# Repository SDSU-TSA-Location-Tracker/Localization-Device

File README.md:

# Localization-Device
This pocket embedded device acts as a local node in a network of anchor nodes and a gateway node. The local device transmits data to the anchor nodes, which measure the RSSI between multiple anchor nodes and the local node to estimate the distance between anchors in the network; this estimation is done through a classification machine learning model. The transmission and receiving of data between local and anchor nodes will be performed using BLE technology. The distance estimation is done at the gateway node, where the RSSI values are sent. One layer up, a holistic system calculates the position of the local node based on the distance from each anchor node. Our design utilizes embedded design with microcontrollers, power and networking components, and networking and machine learning algorithms. 

## Project Team Members
Leonard Chatterton (CompE), Hada Marabeh (EE), Tristan Richmond (CompE), Sri Shatagopam (CompE), Zachary Rocha (EE)
 
## How to Contribute to the Repository
Here is a brief explanation on how to contribute git and github

#### Git vs. Github
Git is a repository version control that is local to your computer only. This means only the user of the local computer has access to these files. It keeps track of any changes that are commited to it so that each iteration of a repo can be accessed. Be sure to update this each time you finish your work session for the day as it will act as a backup storage. Git is important for version control but also because this is where github will be pulling the files from whenever a "push" occurs. **You will need to install git onto your computer**

https://git-scm.com/downloads

Github is a cloud based repository viewer that holds allows a repository to be accessed via webapp. Github will act as a central location for all our individual tasks and develepments to be accessed from any computer connected to the internet. Changes should be comitted to Git first and then it is pushed to Github so anybody can access the actual files. 

#### Cloning
To make the initial link of a github repository onto your git, you must clone it. Here are the steps to doing so

1. Open git bash or linux terminal in the working directory of where you wish to store the repository files on your computer. This is can be done by right-clicking inside the folder you save the files and selecting "Git Bash Here"

2. Use the clone command to clone the github repository onto your git. It will automatically create a folder with the name of the repository with all of its contents
```
git clone https://github.com/SDSU-TSA-Location-Tracker/Localization-Device.git
```

#### Branching
Every repository, in our case **Localization-Device**, has a **main** branch where the most up-to-date ready to ship version is held. This is to ensure there is always a deployable version at any point in the development and maintenance cycle. When new features or additions are being developed, typically a new branch is created with the name of that feature. This allows for a new location that new code and updates can be saved without affecting the **main** branch. In our case, there currently exists a branch for each seperate piece to the project. Once one of the features/branches has been thoroughly tested and is stable, that branch is merged into the **main** branch. What this will do is copy all files from the initial development branch and merge them into the **main** branch so it becomes the most up-to-date version with these new features.

Here is an example of how to create a new branch off of main. Please use the following naming format for the branch **[Your_Name]_[Description of Branch]**

#### Github Branch Example

Create a new branch off of **RaspberryPi** called "Tristan_RaspberryPi_PCB_Design"

```
git checkout -b Tristan_RaspberryPi_PCB_Design RaspberryPi
```

#### Git Workflow

Here is a step by step explanation of how a typical worksession goes

1. Open git bash or linux terminal in the working directory of where you store the repository files on your computer. This is can be done by right-clicking inside the folder you save the files and selecting "Git Bash Here"

2. Pull any and all changes from the github repository **main** to be saved into your local git. Note you must enter the exact branches you wish to update your local version of to the github version. See step 3 on how to change current branch. 
```
git pull origin [Name_of_Branch]
```

3. Enter the exact branch you wish to do development in. Important to do this step as failure to do so may result in conflicts
```
git checkout [Name_of_Branch]
```

4. Start developing as you normally do until you are all finished

5. Add the specific files that were worked
```
git add file.txt
```

6. Commit the changes to the added files to the local git with a message of what was changed. It is important to add a message as the commit will open up VIM expecting you to write a message in. **To avoid this issue, be sure to write the message in the initial commit command**
```
git commit -m "Programmed the Arduino to blink an LED every 5 seconds"
```

7. Push these commits in your local git to the github so everyone can pull these changes to their local computers
```
git push origin [Name_of_Branch]
```

8. A pop window will appear prompting for you github login information. Enter you username into the first window and click submit, then enter you password into the second window and click submit.

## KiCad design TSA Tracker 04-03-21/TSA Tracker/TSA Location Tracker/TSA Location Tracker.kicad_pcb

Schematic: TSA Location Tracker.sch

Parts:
Arduino1: Arduino-NANO-33; NANO_33_Socket_Castell
D1: LED; LED_D3.0mm
H1, H2, H3, H4: MountingHole_Pad; MountingHole_2.7mm_M2.5_Pad
LED_Switch1: SW_SPST; SW_PUSH_6mm
Mode_Switch1: SW_SP3T; E-Switch-EG1313-0
Power_Switch1: SW_DPDT_x2; SW_CuK_JS202011AQN_DPDT_Angled
R1, R2, R3, R5: 10k; R_0603_1608Metric_Pad1.05x0.95mm_HandSolder
R4: 330; R_0603_1608Metric_Pad1.05x0.95mm_HandSolder
U1: AdafruitCharger; AdafruitMiniLipo

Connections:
GND: Arduino1.14, H1.1, H2.1, H3.1, H4.1, R1.2, R2.2, R3.2, R5.2, U1.2, U1.3
unnamed: Arduino1.2, LED_Switch1.2, Mode_Switch1.3, Power_Switch1.3 (C)
unnamed: Arduino1.19, D1.1 (K)
unnamed: Arduino1.20, R4.2
unnamed: Arduino1.21, LED_Switch1.1, R5.1
unnamed: Arduino1.26, Mode_Switch1.4, R1.1
unnamed: Arduino1.27, Mode_Switch1.2, R2.1
unnamed: Arduino1.28, Mode_Switch1.1, R3.1
unnamed: D1.2 (A), R4.1
unnamed: Power_Switch1.2 (B), U1.4

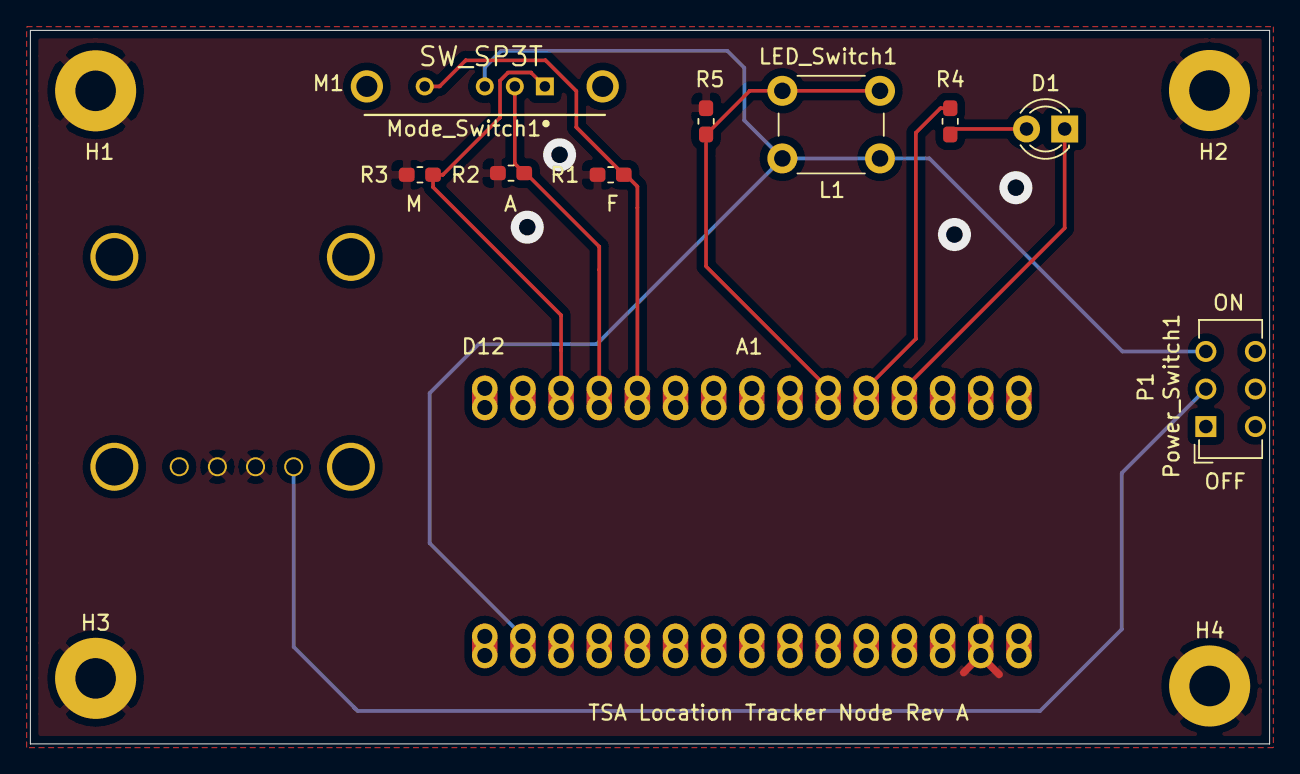
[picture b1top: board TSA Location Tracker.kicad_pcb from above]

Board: 2 copper layers, 82.5 x 47.5 mm, 15 parts (1 on the bottom side), 10 nets.

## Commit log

2021-03-17 Old version
2021-03-17 Added data routine, PCB verification, and node firmware files
2021-03-17 Added RaspberryPi scan firmware
2021-03-19 Fixed RSSI value format to '-70'
2021-03-26 working data collection update
2021-03-30 Data Routine mode switch features
2021-03-30 In progress changes to Node Firmware
2021-03-30 Scan for all BLE devices on RPi4
2021-03-31 Node firmware multi mode integration in progress
2021-04-02 Data collection debugging
2021-04-02 MQTT and updated bluepy scripts
2021-04-02 Fixed Node Firmware to detect and serially print RSSI of other nodes
2021-04-04 Added Node PCB Folder
2021-04-04 Updated switch to push button symbol
2021-04-07 small fixes
2021-04-07 Fixed Manufacturer Data to hold name+rssi of mobile nodes
2021-04-07 Updated Sri's bleclass.py
2021-04-13 increased advertising duration and efficency
2021-04-18 scan 1 second duty cycle
2021-04-19 scan for name instead of MAC
2021-04-19 Reverted to working Node firmware
2021-04-21 Model, Data, and BLEscan
2021-04-21 Test GUI app
2021-04-21 Added intialization for manufacturing data
2021-04-21 Added model and gui
2021-04-21 new ip
2021-04-22 First push
2021-04-28 Delay adjustments
2021-04-28 Write to File Update and empty set check
2021-04-29 GUI Update working
2021-04-29 small adjustments
2021-04-29 Added Enclosure Files
2021-05-03 Added log equation ble
2021-05-03 small tests
2021-05-03 added ML driver
2021-05-04 GUI update: Can start/stop/pause/resume, start time and time elapsed
2021-05-05 Reorganized PCB folder
2021-05-05 Added anchor comment selection
2021-05-05 reorganized GUI files
2021-05-05 Organized data and pi files
2021-05-05 RaspberryPi Firmware
2021-05-06 updated files
2021-05-06 Added data files
2021-05-06 gui files
2021-05-06 Revert "Tristan arduino ble"
2021-05-06 Included all project files
